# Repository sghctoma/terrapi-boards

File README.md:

# TerraPi boards

PCB designs for various sensors, controls, etc. used with TerraPi

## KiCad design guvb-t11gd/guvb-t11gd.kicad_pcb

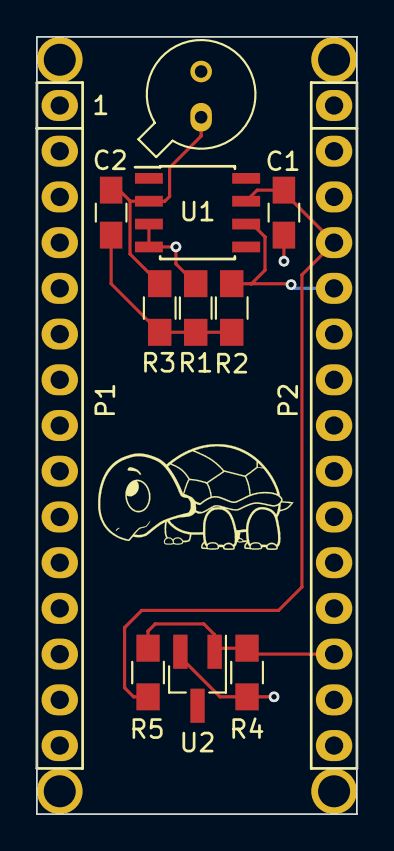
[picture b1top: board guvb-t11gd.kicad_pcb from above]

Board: 2 copper layers, 17.8 x 43.2 mm, 16 parts (0 on the bottom side), 6 nets.

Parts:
C1: 0.1uF; C_0805_HandSoldering
C2: 10nF; C_0805_HandSoldering
D1: D_Photo; TO-46-2_Window
P1: Digital; Socket_Strip_Arduino_1x15
P2: Analog; Socket_Strip_Arduino_1x15
P3, P4, P5, P6: CONN_01X01; 1pin_Nano
R1: 11K; R_0805_HandSoldering
R2: 1K; R_0805_HandSoldering
R3: 10M; R_0805_HandSoldering
R4: 10K; R_0805_HandSoldering
R5: 750; R_0805_HandSoldering
U1: LMC6081IM; SOIC-8_3.9x4.9mm_Pitch1.27mm
U2: LM4040; SOT-23_Handsoldering

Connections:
+5V: C1.2, P2.4, R5.1, U1.7
/A7: P2.5, R1.2, U1.6
/AREF: P2.13, R4.1, R5.2, U2.1
GND: C1.1, D1.2, P1.4, P2.2, R2.1, R4.2, U1.3, U1.4, U2.2
unnamed: C2.1, R1.1, R2.2, R3.1
unnamed: C2.2, D1.1, R3.2, U1.2

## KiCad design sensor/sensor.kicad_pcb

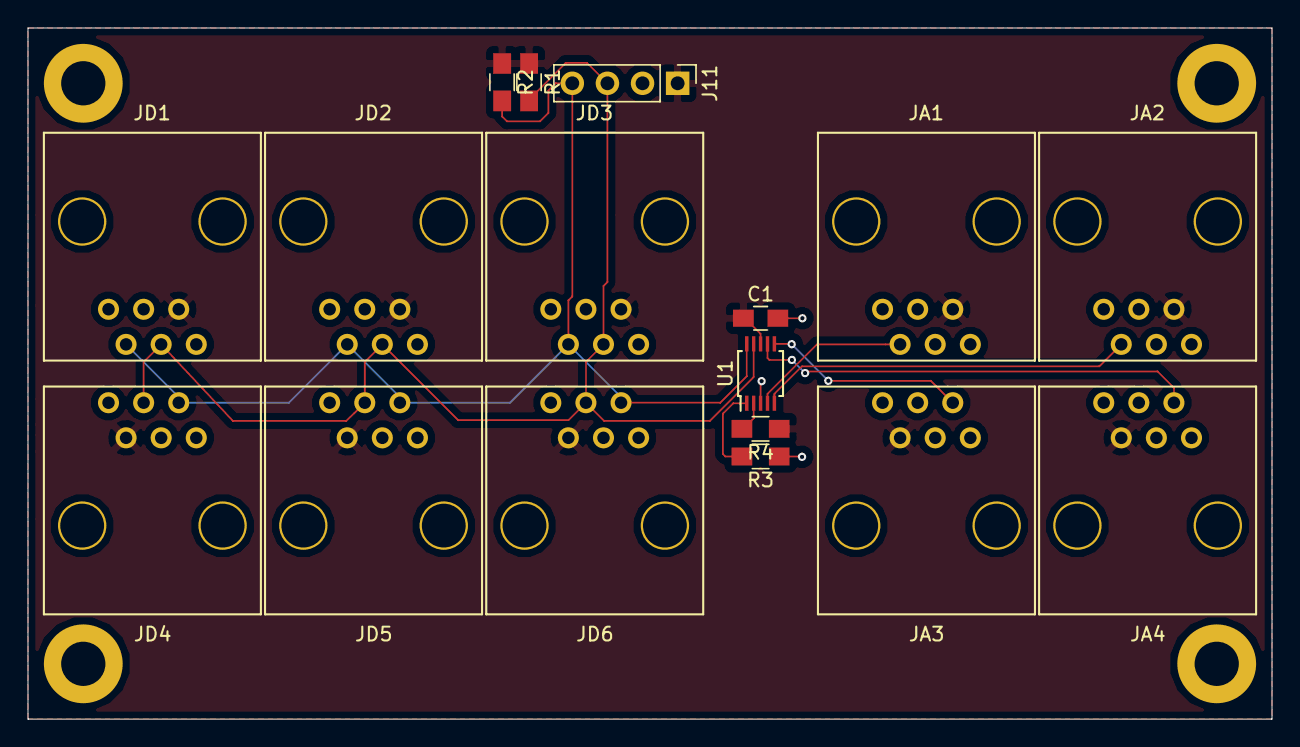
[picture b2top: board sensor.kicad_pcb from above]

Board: 2 copper layers, 90.0 x 50.0 mm, 17 parts (0 on the bottom side), 10 nets.

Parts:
C1: 1uF; C_0805_HandSoldering
J11: Conn_01x04; Pin_Header_Straight_1x04_Pitch2.54mm
JA1, JA2, JA3, JA4: 5222-6P6C
JD1, JD2, JD3, JD4, JD5, JD6: 5222-6P6C
R1, R2, R3, R4: 10K; R_0805_HandSoldering
U1: ADS1015IDGST; TSSOP-10_3x3mm_Pitch0.5mm

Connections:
+3V3: C1.1, J11.1, JA1.2, JA2.2, JA3.2, JA4.2, JD1.2, JD2.2, JD3.2, JD4.2, JD5.2, JD6.2, R1.1, R2.1, R4.1, U1.8
/AIN0: JA1.5, U1.4
/AIN1: JA2.5, U1.5
/AIN2: JA3.5, U1.6
/AIN3: JA4.5, U1.7
/SCL: J11.4, JD1.5, JD2.5, JD3.5, JD4.5, JD5.5, JD6.5, R2.2, U1.10
/SDA: J11.3, JD1.3, JD2.3, JD3.3, JD4.3, JD5.3, JD6.3, R1.2, U1.9
GND: C1.2, J11.2, JA1.3, JA2.3, JA3.3, JA4.3, JD1.4, JD2.4, JD3.4, JD4.4, JD5.4, JD6.4, R3.1, U1.3
unnamed: R3.2, U1.1
unnamed: R4.2, U1.2

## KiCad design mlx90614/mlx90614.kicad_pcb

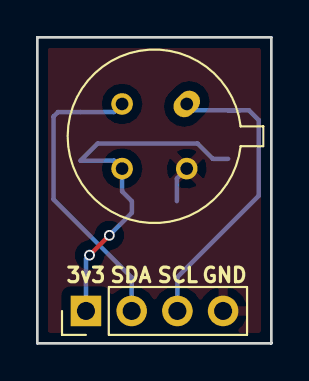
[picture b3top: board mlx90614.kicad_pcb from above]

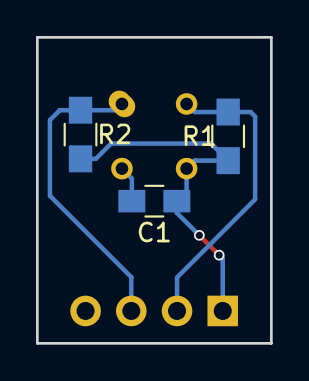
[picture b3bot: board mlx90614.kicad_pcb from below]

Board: 2 copper layers, 13.0 x 17.0 mm, 5 parts (3 on the bottom side), 4 nets.

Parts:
C1: 0.1uF; C_0805_HandSoldering
J1: Conn_01x04; Pin_Header_Straight_1x04_Pitch2.54mm
R1, R2: 10K; R_0805_HandSoldering
U1: MLX90614; TO-39-4_Window

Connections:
+3V3: C1.1, J1.1, R1.1, R2.1, U1.3
/SCL: J1.3, R2.2, U1.1
/SDA: J1.2, R1.2, U1.2
GND: C1.2, J1.4, U1.4

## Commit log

2018-05-20 Added MLX90614 IR heat sensor breakout board.
2018-05-20 Added footprint for iENK Electronic 5222 RJ11-6P/6C connector
2018-05-20 Added datasheet link fot the Melexis MLX90614
2018-05-20 Moved custom libraries from "common" folder under project folders.
2018-05-20 Added GUVB-T11GD Arduino Nano shield.
2018-05-20 Added GUVB-S11SD Arduino Nano shield.
2018-05-21 Added connector board for sensors
2018-05-23 Added turtle graphics.
